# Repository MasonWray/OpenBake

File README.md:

# OpenBake
Open source hardware and software for converting a consumer-grade toaster oven into a reflow oven.

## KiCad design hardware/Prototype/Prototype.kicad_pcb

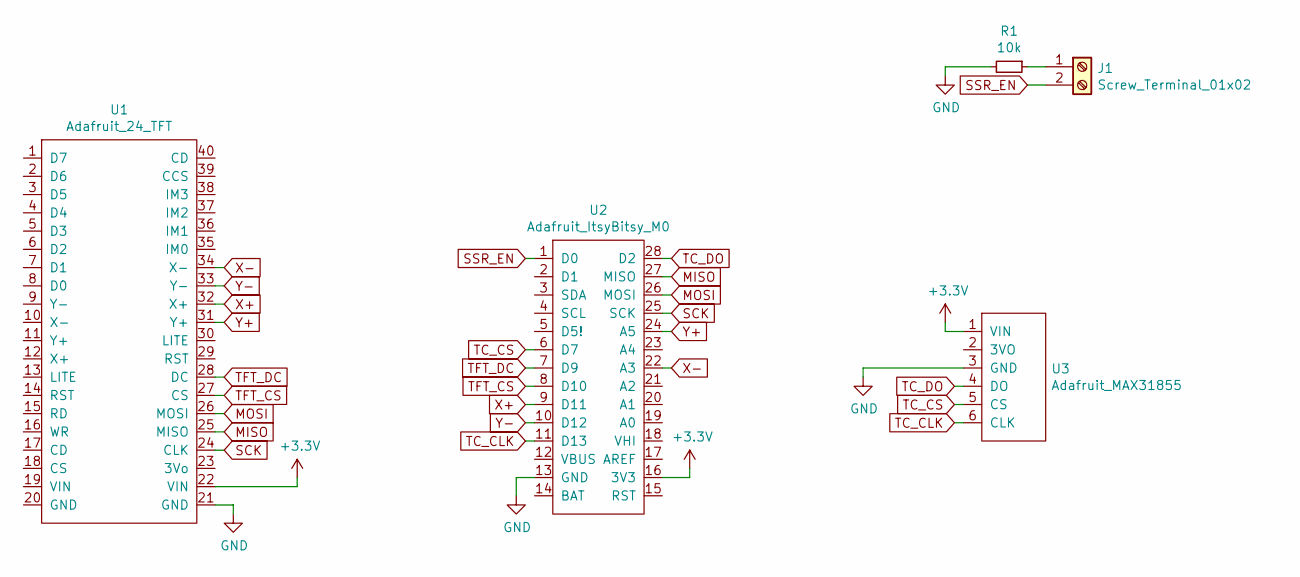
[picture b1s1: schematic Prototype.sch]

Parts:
J1: Screw_Terminal_01x02; TerminalBlock_Altech_AK300-2_P5.00mm
R1: 10k; R_Axial_DIN0411_L9.9mm_D3.6mm_P15.24mm_Horizontal
U1: Adafruit_24_TFT
U2: Adafruit_ItsyBitsy_M0
U3: Adafruit_MAX31855

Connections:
+3V3: U1.22 (VIN), U2.16 (3V3), U3.1 (VIN)
GND: R1.2, U1.21 (GND), U2.13 (GND), U3.3 (GND)
MISO: U1.25 (MISO), U2.27 (MISO)
MOSI: U1.26 (MOSI), U2.26 (MOSI)
unnamed: J1.1, R1.1
SCK: U1.24 (CLK), U2.25 (SCK)
SSR_EN: J1.2, U2.1 (D0)
TC_CLK: U2.11 (D13), U3.6 (CLK)
TC_CS: U2.6 (D7), U3.5 (CS)
TC_DO: U2.28 (D2), U3.4 (DO)
TFT_CS: U1.27 (CS), U2.8 (D10)
TFT_DC: U1.28 (DC), U2.7 (D9)
X+: U1.32 (X+), U2.9 (D11)
X-: U1.34 (X-), U2.22 (A3)
Y+: U1.31 (Y+), U2.24 (A5)
Y-: U1.33 (Y-), U2.10 (D12)

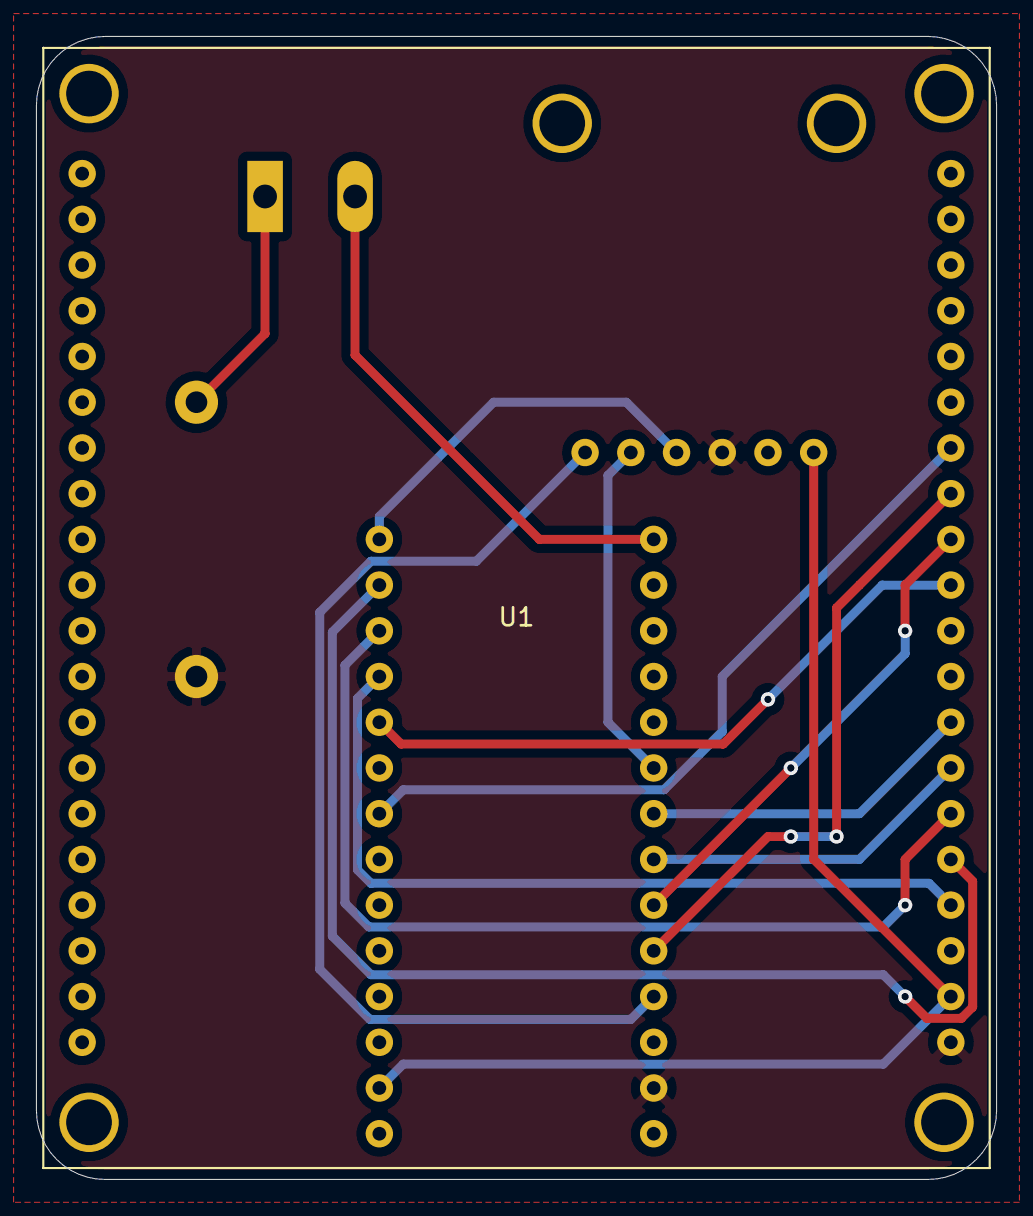
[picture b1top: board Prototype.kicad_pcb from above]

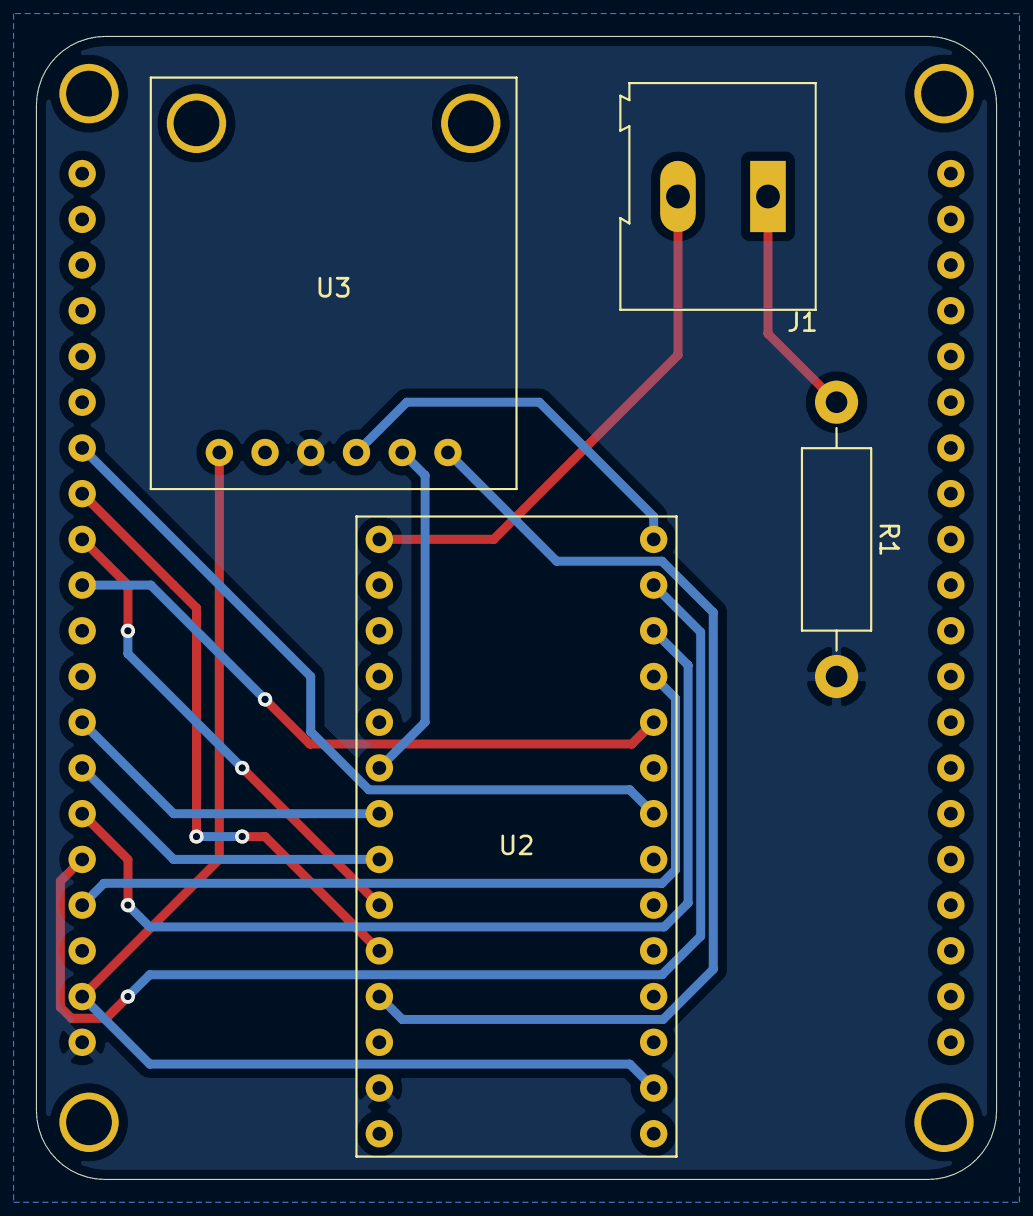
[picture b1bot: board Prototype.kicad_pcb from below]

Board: 2 copper layers, 53.3 x 63.5 mm, 5 parts (4 on the bottom side), 16 nets.

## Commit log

2022-09-14 Create firmware project
2022-09-14 Reduce DotStar brightness on startup
2022-09-14 Initialize TFT
2022-09-14 Initialize touch screen
2022-09-15 Create View abstract class
2022-09-15 Implement view renderer framework
2022-09-15 View Renderer Framework (#3)
    * Create View abstract class
    * Implement view renderer framework
2022-09-15 Add main UI components
2022-09-16 Move DotStar driver from heap to stack
2022-09-16 Move TouchScreen driver from heap to stack
2022-09-16 Move TFT driver from heap to stack
2022-09-16 Cleanup
2022-09-16 Inject drivers into Main View controller
2022-09-16 Display temp on main view
2022-09-16 Use BoundingBox struct to position Main UI buttons
2022-09-16 Handle button pressed on main UI
2022-09-17 Create Main UI View (#5)
    * Add main UI components
    * Move DotStar driver from heap to stack
    * Move TouchScreen driver from heap to stack
    * Move TFT driver from heap to stack
    * Cleanup
    * Inject drivers into Main View controller
2022-09-17 Create KiCAD project
2022-09-17 Create Module symbol library
2022-09-17 Create TFT display symbol
2022-09-17 Create Adafruit M0 symbol
2022-09-17 Create TC amp symbol
2022-09-17 Create module prototype board schematic
2022-09-17 Create Prototype Hardware Schematic (#12)
    * Create KiCAD project
    * Create Module symbol library
    * Create TFT display symbol
    * Create Adafruit M0 symbol
    * Create TC amp symbol
    * Create module prototype board schematic
2022-09-18 Return view type from main UI render loop
2022-09-18 Rename View Utils
2022-09-18 Restructure ViewUtils and View
2022-09-18 Move ViewType enum into View base class
2022-09-18 Switch to config view when config is pressed
2022-09-18 Active View Switcher (#14)
    * Return view type from main UI render loop
    * Rename View Utils
    * Restructure ViewUtils and View
    * Move ViewType enum into View base class
    * Switch to config view when config is pressed
2022-09-23 Add navigation tree to nav view
2022-09-23 Use ConfigListItem class to display list items
2022-09-23 Git fixup
2022-09-23 Render forward and back arrows
2022-09-23 Construct List items iteratively
2022-09-24 Make space for back button at top of page
2022-09-24 Render special back button
2022-09-24 Add button press animation to list items
2022-09-24 Bounding box init in helper function
2022-09-24 Add navigation to list items
2022-09-24 Nav List View (#16)
    * Add navigation tree to nav view
    * Use ConfigListItem class to display list items
    * Git fixup
    * Render forward and back arrows
    * Construct List items iteratively
    * Make space for back button at top of page
2022-09-24 Add TFT footprint
2022-09-24 Add ItsyBitsy M0 footprint
2022-09-24 Create Thermocouple footprint
2022-09-24 Create prototype board layout
2022-09-24 Create Prototype Board Layout (#18)
    * Add TFT footprint
    * Add ItsyBitsy M0 footprint
    * Create Thermocouple footprint
    * Create prototype board layout
2022-09-24 Add splash screen
2022-09-24 Add splash screen (#19)
2022-09-24 Create solder profile model
2022-09-24 Add profile to AppState container
2022-09-25 Add AppState to main view
2022-09-25 Application State Container Object (#22)
    * Create solder profile model
    * Add profile to AppState container
    * Add AppState to main view
2022-09-25 Add SSR connector to controller board
2022-09-25 Add SSR connector to controller board (#23)
2022-09-25 Navigate to profile selector view
2022-09-25 Create reusable button component
2022-09-25 Implement button press highlighting
2022-09-25 Select solder profiles
2022-09-25 Profile Selector View (#24)
    * Navigate to profile selector view
    * Create reusable button component
    * Implement button press highlighting
    * Select solder profiles
2022-09-25 Restructure component filter
2022-09-26 Draw target curve
2022-09-26 Temp Chart Component Ideal Curve (#27)
    * Restructure component filter
    * Draw target curve
2022-09-26 Use button components
2022-09-26 Use Button Components (#29)
2022-09-26 Create KeyVal component
2022-09-26 Draw Keys
2022-09-26 Display values
2022-09-26 Dynamic temp updates
2022-09-26 Use KeyVal Component in Main View (#31)
    * Create KeyVal component
    * Draw Keys
    * Display values
    * Dynamic temp updates
2022-09-27 Draw actual temp on chart
2022-09-27 Temp Chart Actual Curve (#36)
    * Cleanup
    * Draw actual temp on chart
2022-09-27 Check for profile before starting cycle
2022-09-27 Update mins and secs in KeyVal
2022-09-27 Fix string formatting
2022-09-27 Update Time KeyVal While Running (#37)
    * Check for profile before starting cycle
    * Update mins and secs in KeyVal
    * Fix string formatting
2022-09-27 Fix Main View temp display
2022-09-27 Fix Main View temp display (#38)
2022-09-27 Update Button.cpp (#39)
2022-09-27 Update Button.cpp (#40)
2022-09-27 Create temp controller
2022-09-27 Create Temp Controller class stubs
2022-09-27 Implement Temp Controller update function
2022-09-27 Select current temp zone from Solder Profile
2022-09-27 Calculate target temp
2022-09-27 Update temp controller from main loop
2022-09-27 Control Temp Relay from Solder Profile (#41)
    * Create temp controller
    * Create Temp Controller class stubs
    * Implement Temp Controller update function
    * Select current temp zone from Solder Profile
    * Calculate target temp
    * Update temp controller from main loop
2022-09-30 Create LICENSE.md (#42)
2022-09-30 Update start button text on press
2022-09-30 Encapsulate button draw function
2022-09-30 Fix button double-render
2022-09-30 Renamed defaults
2022-10-01 Clear old temp chart when restarting process
2022-10-01 Main View Contextual Styling (#51)
    * Update start button text on press
    * Encapsulate button draw function
    * Fix button double-render
    * Renamed defaults
    * Update MainView.cpp
    * Clear old temp chart when restarting process
2022-10-01 Change CONFIG name
2022-10-01 Transition Directly to Profile Selector (#52)
    * Update MainView.cpp
    * Change CONFIG name
2022-10-01 v0.1.0 (#53)
    * Create firmware project
    * Reduce DotStar brightness on startup
    * Initialize TFT
    * Initialize touch screen
    * View Renderer Framework (#3)
    * Create View abstract class
2022-10-01 Serial Fix
2022-10-01 v0.1.0 (#54)
2022-10-01 Create renamed project structure
2022-10-01 Add Button
2022-10-01 Add KeyVal
2022-10-01 Add TempChart
2022-10-01 Add TempController
2022-10-01 Add Display Interface
2022-10-01 Add data models
2022-10-01 Add view Components
2022-10-01 Change name in firmware
2022-10-01 Remove old firmware project
2022-10-01 v0.1.1 (#55)
    * Update openbake-fw.vcxproj
    * Create renamed project structure
    * Add Button
    * Add KeyVal
    * Add TempChart
    * Add TempController
2024-05-17 push up for git restructure
